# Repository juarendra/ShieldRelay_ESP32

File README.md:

# ShieldRelay_ESP32
Relay Shield for ESP32 , Nodemcu V2 Amica or Nodemcu V3 Lolin. In board there are 5 Relay and 3 type of Relay, first is 30A Relay Coil, second is 10 A Relay Coil and third is SSR 2A. And there are full extend header of Microcontroller. the power using Stepdown LM2596 with output 5V 3A and Input 5-30VDC. 

## Spesification ShieldRelay_ESP32
- Input Power 5-30VDC and stepdown to 5VDC
- PTC Fuse
- INPUT HEADER
- VCC HEADER
- VCC Selector 3v3 or 5V
- Supported ESP32 DEV KIT, NODEMCU V2 or V3
- Pin Header GPIO with Servo Formated
- 1 x 30A Relay Coil
- 2 x 10A Relay Couil
- 2 x 2A SSR

# Privew Hardware ShieldRelay_ESP32
<p align="center">

</p>

# Documentation 
- [Dimension](https://github.com/juarendra/ShieldRelay_ESP32/blob/main/HARDWARE/dimension_shield_esp32.pdf)
- [BOM](https://github.com/juarendra/ShieldRelay_ESP32/blob/main/DOC/BOM_shieldRelay.csv)

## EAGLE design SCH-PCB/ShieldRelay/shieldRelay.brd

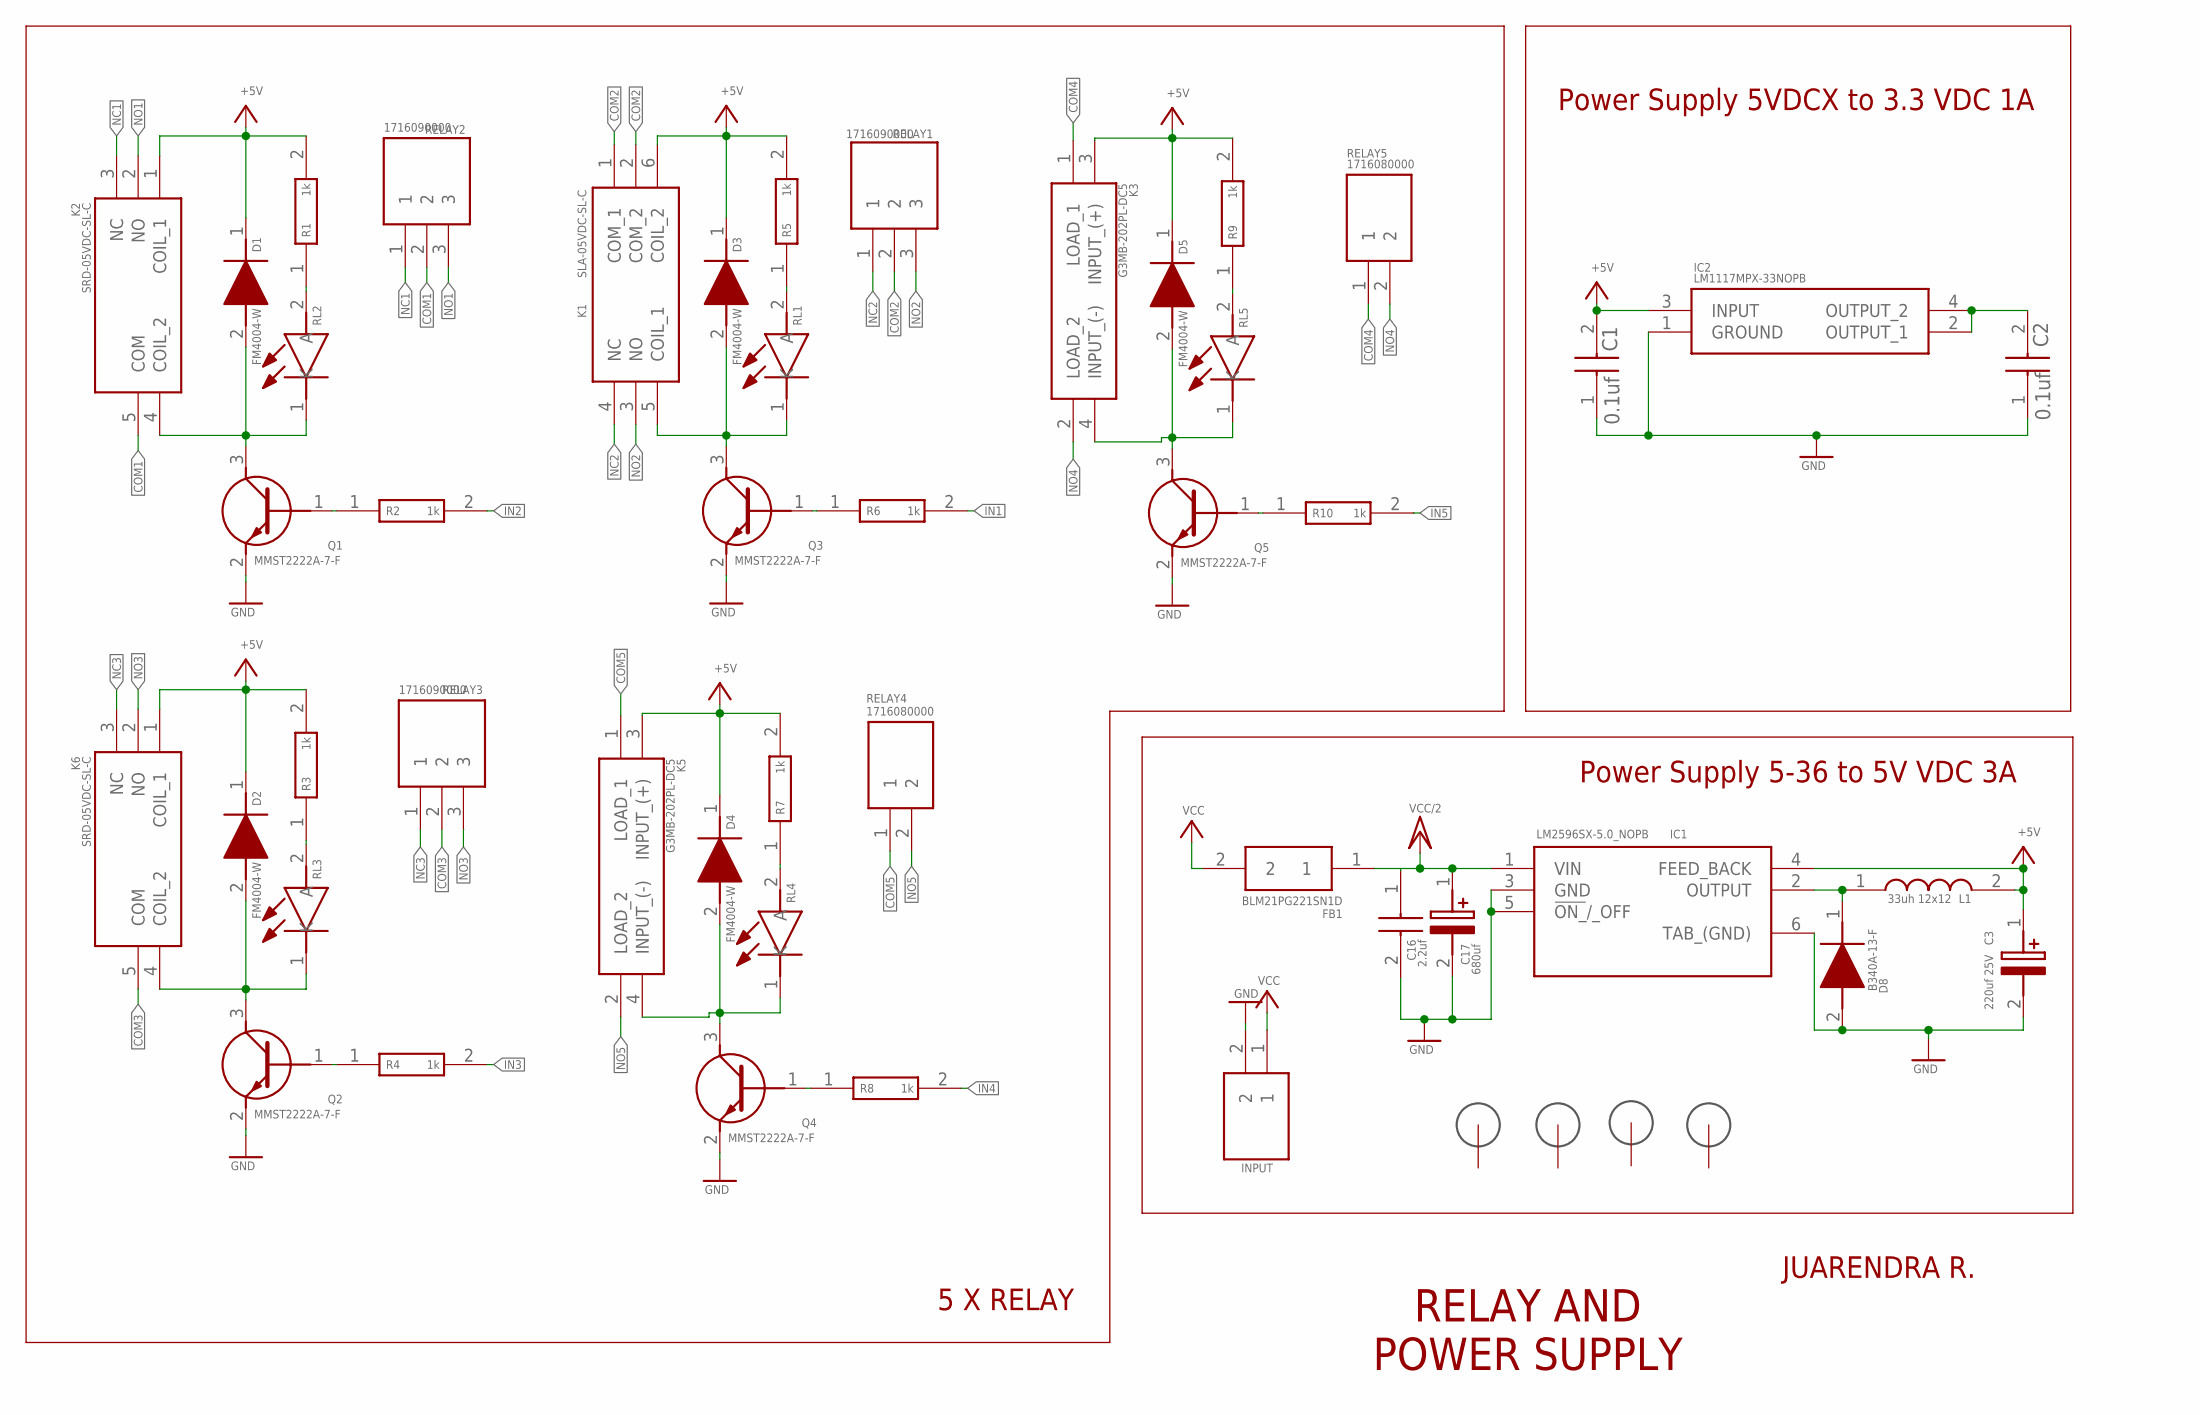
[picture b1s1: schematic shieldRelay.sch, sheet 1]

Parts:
C1, C2: 0.1uf; CAPC1608X95N
C3: 220uf 25V; CAPPRD350W60D850H1250
C16: 2.2uf; CAPC2012X140N
C17: 680uf; EEHZS1H221P
D1, D2, D3, D4, D5: FM4004-W; DIONM5025X231N
D8: B340A-13-F; DIOM5226X240N
FB1: BLM21PG221SN1D; BEADC2012X105N
H1, H2, H3, H4: 3MM_HOLE
IC1: LM2596SX-5.0_NOPB; KTT0005B
IC2: LM1117MPX-33NOPB; SOT230P700X180-4N
INPUT: 1759017; SHDRRA2W103P0X508_1X2_1016X120
K1: SLA-05VDC-SL-C; SLA05VDCSLC
K2, K6: SRD-05VDC-SL-C; SRD05VDCSLC
K3, K5: G3MB-202PL-DC5; G3MB202PLDC5
L1: 33uh 12x12; WE-PD_1260/1245/1280/121054
Q1, Q2, Q3, Q4, Q5: MMST2222A-7-F; SOT65P210X110-3N
R1, R2, R3, R4, R5, R6, R7, R8, R9, R10: 1k; ERA3AEB101V
RELAY1, RELAY2, RELAY3: 1716090000; SHDR3W95P0X508_1X3_1524X1000X1
RELAY4, RELAY5: 1716080000
RL1, RL2, RL3, RL4, RL5: 150080SS75000; LEDC2012X80N

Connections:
+5V: C1.2, C3.1 (+), D1.1 (K), D2.1 (K), D3.1 (K), D4.1 (K), D5.1 (K), IC1.4 (FEED_BACK), IC2.3 (INPUT), K1.6 (COIL_2), K2.1 (COIL_1), K3.3 (INPUT_(+)), K5.3 (INPUT_(+)), K6.1 (COIL_1), L1.2, R1.2, R3.2, R5.2, R7.2, R9.2; also elsewhere on the board
COM1: K2.5 (COM), RELAY2.2
COM2: K1.1 (COM_1), K1.2 (COM_2), RELAY1.2
COM3: K6.5 (COM), RELAY3.2
COM4: K3.1 (LOAD_1), RELAY5.1
COM5: K5.1 (LOAD_1), RELAY4.1
GND: C1.1, C2.1, C3.2 (-), C16.2, C17.2 (-), D8.2 (A), IC1.3 (GND), IC1.5 (!ON_!/_OFF), IC1.6 (TAB_(GND)), IC2.1 (GROUND), INPUT.2, Q1.2 (E), Q2.2 (E), Q3.2 (E), Q4.2 (E), Q5.2 (E); also elsewhere on the board
IN1: R6.2; also elsewhere on the board
IN2: R2.2; also elsewhere on the board
IN3: R4.2; also elsewhere on the board
IN4: R8.2; also elsewhere on the board
IN5: R10.2; also elsewhere on the board
unnamed: R3.1, RL3.2 (A)
unnamed: R1.1, RL2.2 (A)
unnamed: D1.2 (A), K2.4 (COIL_2), Q1.3 (C), RL2.1 (K)
unnamed: Q1.1 (B), R2.1
unnamed: D2.2 (A), K6.4 (COIL_2), Q2.3 (C), RL3.1 (K)
unnamed: Q2.1 (B), R4.1
unnamed: R5.1, RL1.2 (A)
unnamed: D3.2 (A), K1.5 (COIL_1), Q3.3 (C), RL1.1 (K)
unnamed: Q3.1 (B), R6.1
unnamed: R7.1, RL4.2 (A)
unnamed: D4.2 (A), K5.4 (INPUT_(-)), Q4.3 (C), RL4.1 (K)
unnamed: Q4.1 (B), R8.1
unnamed: R9.1, RL5.2 (A)
unnamed: D5.2 (A), K3.4 (INPUT_(-)), Q5.3 (C), RL5.1 (K)
unnamed: Q5.1 (B), R10.1
unnamed: D8.1 (K), IC1.2 (OUTPUT), L1.1
unnamed: C2.2, IC2.2 (OUTPUT_1), IC2.4 (OUTPUT_2)
NC1: K2.3 (NC), RELAY2.1
NC2: K1.4 (NC), RELAY1.1
NC3: K6.3 (NC), RELAY3.1
NO1: K2.2 (NO), RELAY2.3
NO2: K1.3 (NO), RELAY1.3
NO3: K6.2 (NO), RELAY3.3
NO4: K3.2 (LOAD_2), RELAY5.2
NO5: K5.2 (LOAD_2), RELAY4.2
VCC: FB1.2, INPUT.1
VCC/2: C16.1, C17.1 (+), FB1.1, IC1.1 (VIN); also elsewhere on the board

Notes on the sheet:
Power Supply 5-36 to 5V VDC 3A
5 X RELAY
Power Supply 5VDCX to 3.3 VDC 1A
RELAY AND POWER SUPPLY
JUARENDRA R.

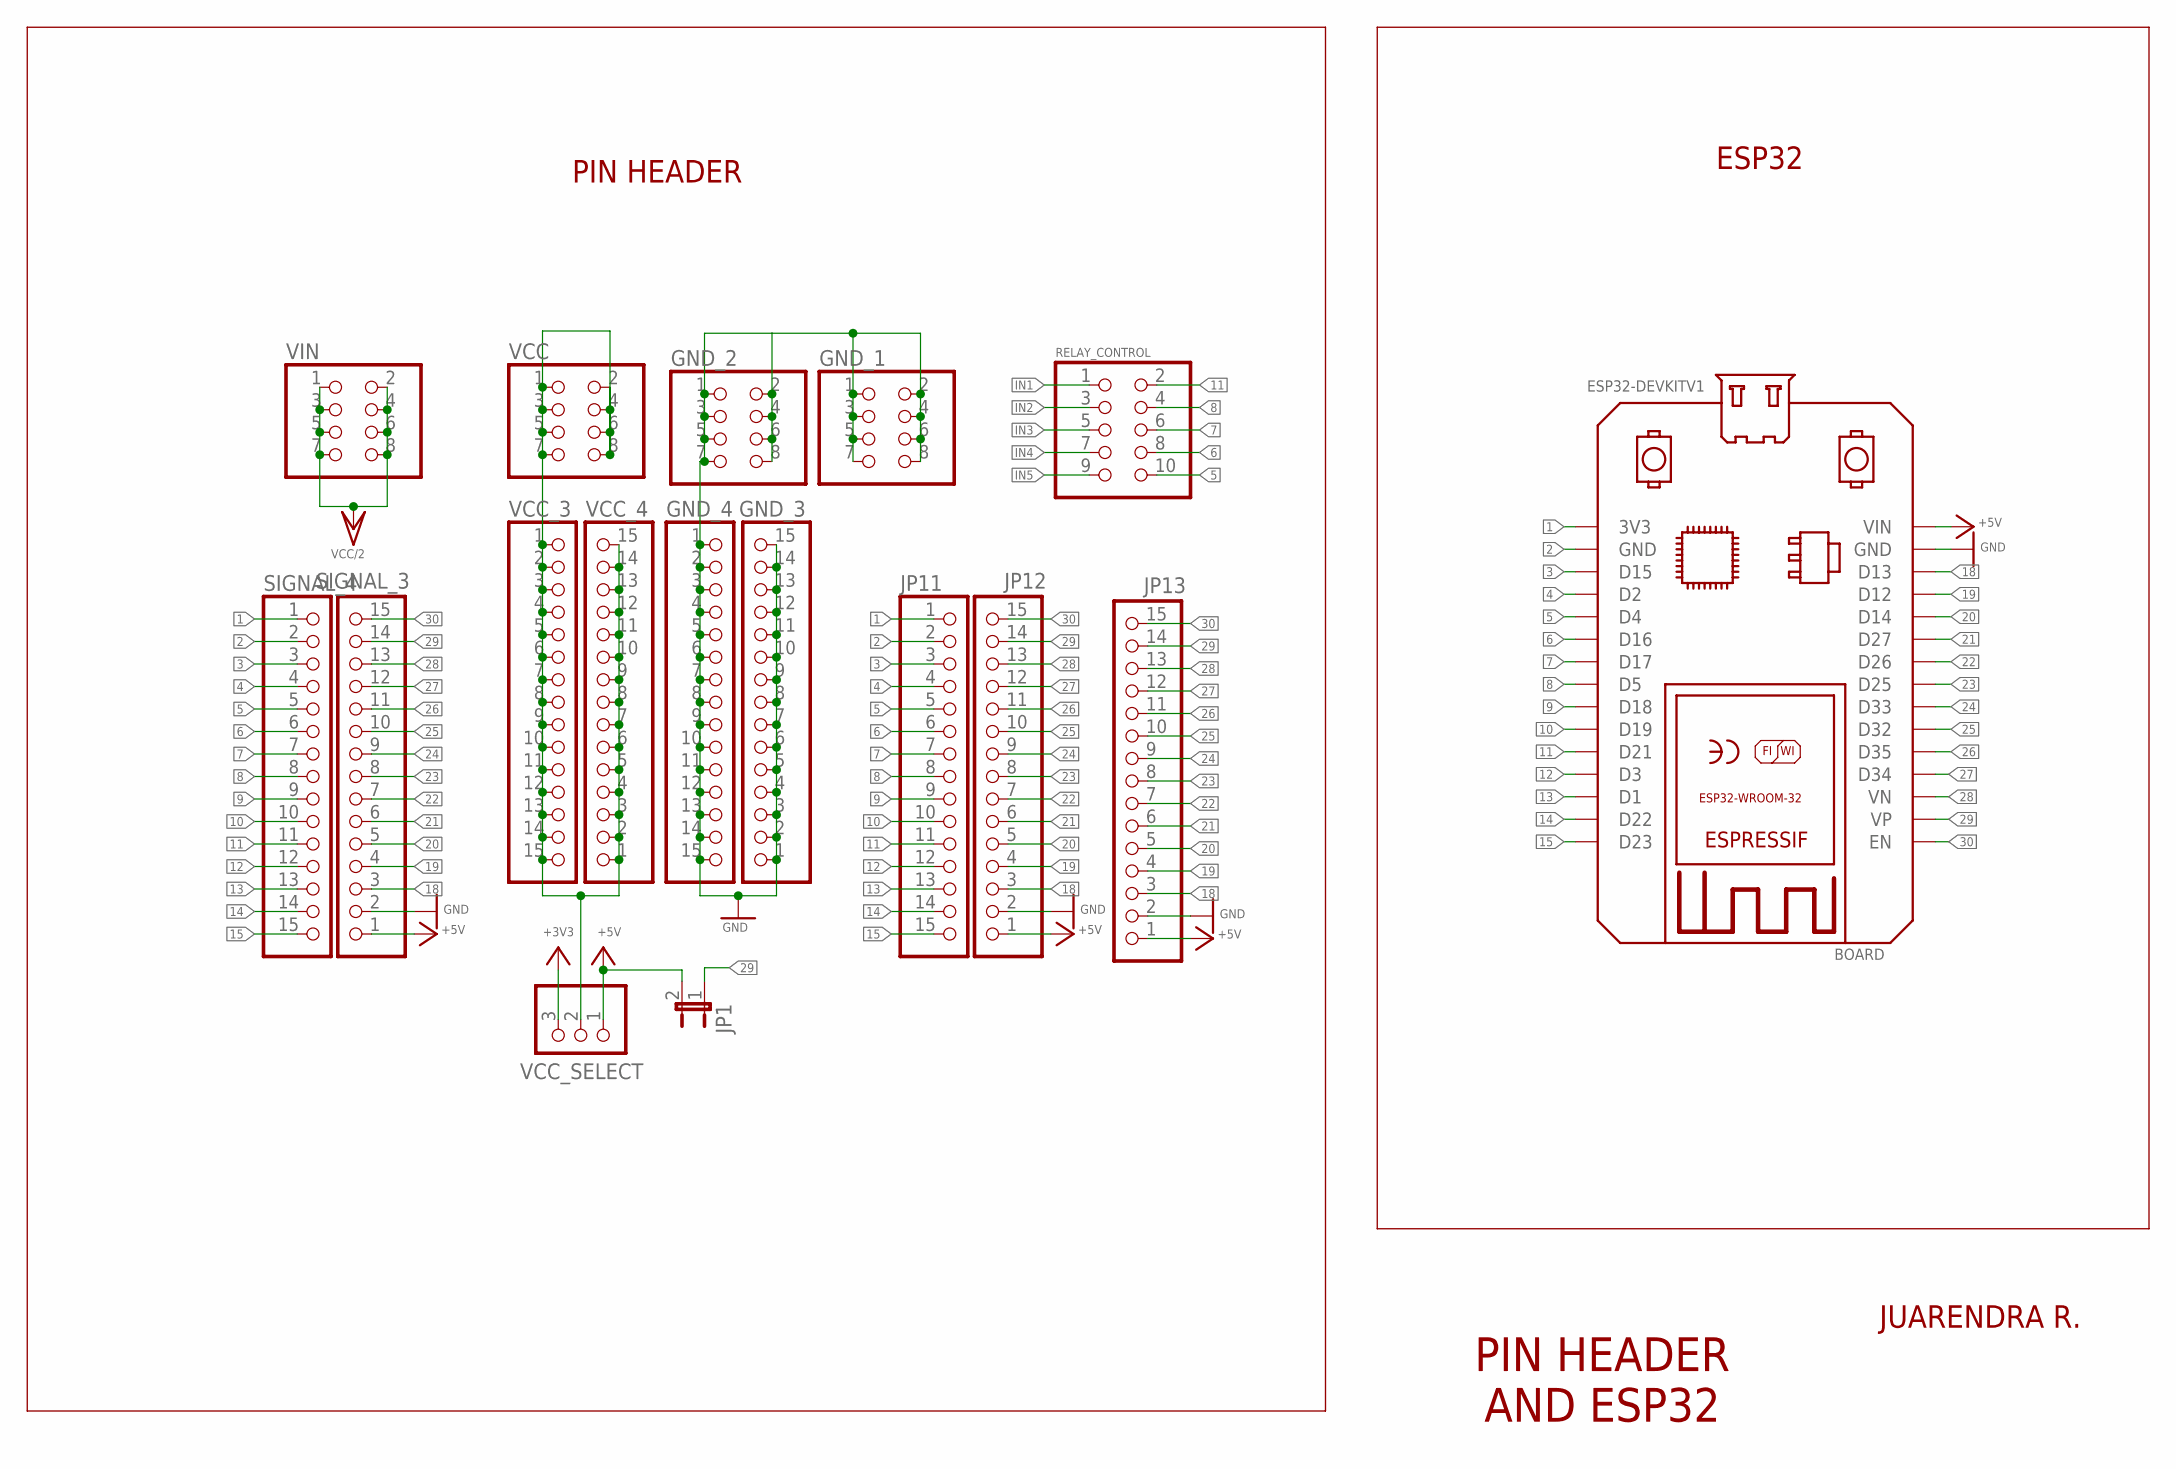
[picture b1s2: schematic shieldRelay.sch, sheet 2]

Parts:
BOARD: ESP32DEVKITV1; ESP32-DEVKITV1
GND_1, GND_2: PINHD-2X4; 2X04
GND_3, GND_4: PINHD-1X15; 1X15
JP1: JP1E; JP1
JP11, JP12, JP13: PINHD-1X15; 1X15
RELAY_CONTROL: PINHD-2X5; 2X05
SIGNAL_3, SIGNAL_4: PINHD-1X15; 1X15
VCC: PINHD-2X4; 2X04
VCC_3, VCC_4: PINHD-1X15; 1X15
VCC_SELECT: PINHD-1X3; 1X03
VIN: PINHD-2X4; 2X04

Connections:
1: BOARD.3V3, JP11.1, SIGNAL_4.1
2: BOARD.GND@1 (GND), JP11.2, SIGNAL_4.2
3: BOARD.D15, JP11.3, SIGNAL_4.3
4: BOARD.D2, JP11.4, SIGNAL_4.4
5: BOARD.D4, JP11.5, RELAY_CONTROL.10, SIGNAL_4.5
6: BOARD.D16, JP11.6, RELAY_CONTROL.8, SIGNAL_4.6
7: BOARD.D17, JP11.7, RELAY_CONTROL.6, SIGNAL_4.7
8: BOARD.D5, JP11.8, RELAY_CONTROL.4, SIGNAL_4.8
9: BOARD.D18, JP11.9, SIGNAL_4.9
10: BOARD.D19, JP11.10, SIGNAL_4.10
11: BOARD.D21, JP11.11, RELAY_CONTROL.2, SIGNAL_4.11
12: BOARD.D3, JP11.12, SIGNAL_4.12
13: BOARD.D1, JP11.13, SIGNAL_4.13
14: BOARD.D22, JP11.14, SIGNAL_4.14
15: BOARD.D23, JP11.15, SIGNAL_4.15
18: BOARD.D13, JP12.3, JP13.3, SIGNAL_3.3
19: BOARD.D12, JP12.4, JP13.4, SIGNAL_3.4
20: BOARD.D14, JP12.5, JP13.5, SIGNAL_3.5
21: BOARD.D27, JP12.6, JP13.6, SIGNAL_3.6
22: BOARD.D26, JP12.7, JP13.7, SIGNAL_3.7
23: BOARD.D25, JP12.8, JP13.8, SIGNAL_3.8
24: BOARD.D33, JP12.9, JP13.9, SIGNAL_3.9
25: BOARD.D32, JP12.10, JP13.10, SIGNAL_3.10
26: BOARD.D35, JP12.11, JP13.11, SIGNAL_3.11
27: BOARD.D34, JP12.12, JP13.12, SIGNAL_3.12
28: BOARD.VN, JP12.13, JP13.13, SIGNAL_3.13
29: BOARD.VP, JP1.1, JP12.14, JP13.14, SIGNAL_3.14
30: BOARD.EN, JP12.15, JP13.15, SIGNAL_3.15
+3V3: VCC_SELECT.3
+5V: BOARD.VIN, JP1.2, JP12.1, JP13.1, SIGNAL_3.1, VCC_SELECT.1; also elsewhere on the board
GND: BOARD.GND, GND_1.1, GND_1.2, GND_1.3, GND_1.4, GND_1.5, GND_1.6, GND_1.7, GND_1.8, GND_2.1, GND_2.2, GND_2.3, GND_2.4, GND_2.5, GND_2.6, GND_2.7, GND_2.8, GND_3.1, GND_3.2, GND_3.3, GND_3.4, GND_3.5, GND_3.6, GND_3.7, GND_3.8, GND_3.9, GND_3.10, GND_3.11, GND_3.12, GND_3.13, GND_3.14, GND_3.15, GND_4.1, GND_4.2, GND_4.3, GND_4.4, GND_4.5, GND_4.6, GND_4.7, GND_4.8, GND_4.9, GND_4.10, GND_4.11, GND_4.12, GND_4.13, GND_4.14, GND_4.15, JP12.2, JP13.2, SIGNAL_3.2; also elsewhere on the board
IN1: RELAY_CONTROL.1; also elsewhere on the board
IN2: RELAY_CONTROL.3; also elsewhere on the board
IN3: RELAY_CONTROL.5; also elsewhere on the board
IN4: RELAY_CONTROL.7; also elsewhere on the board
IN5: RELAY_CONTROL.9; also elsewhere on the board
unnamed: VCC.1, VCC.2, VCC.3, VCC.4, VCC.5, VCC.6, VCC.7, VCC.8, VCC_3.1, VCC_3.2, VCC_3.3, VCC_3.4, VCC_3.5, VCC_3.6, VCC_3.7, VCC_3.8, VCC_3.9, VCC_3.10, VCC_3.11, VCC_3.12, VCC_3.13, VCC_3.14, VCC_3.15, VCC_4.1, VCC_4.2, VCC_4.3, VCC_4.4, VCC_4.5, VCC_4.6, VCC_4.7, VCC_4.8, VCC_4.9, VCC_4.10, VCC_4.11, VCC_4.12, VCC_4.13, VCC_4.14, VCC_4.15, VCC_SELECT.2
VCC/2: VIN.1, VIN.2, VIN.3, VIN.4, VIN.5, VIN.6, VIN.7, VIN.8; also elsewhere on the board

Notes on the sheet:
PIN HEADER AND ESP32
JUARENDRA R.
PIN HEADER
ESP32

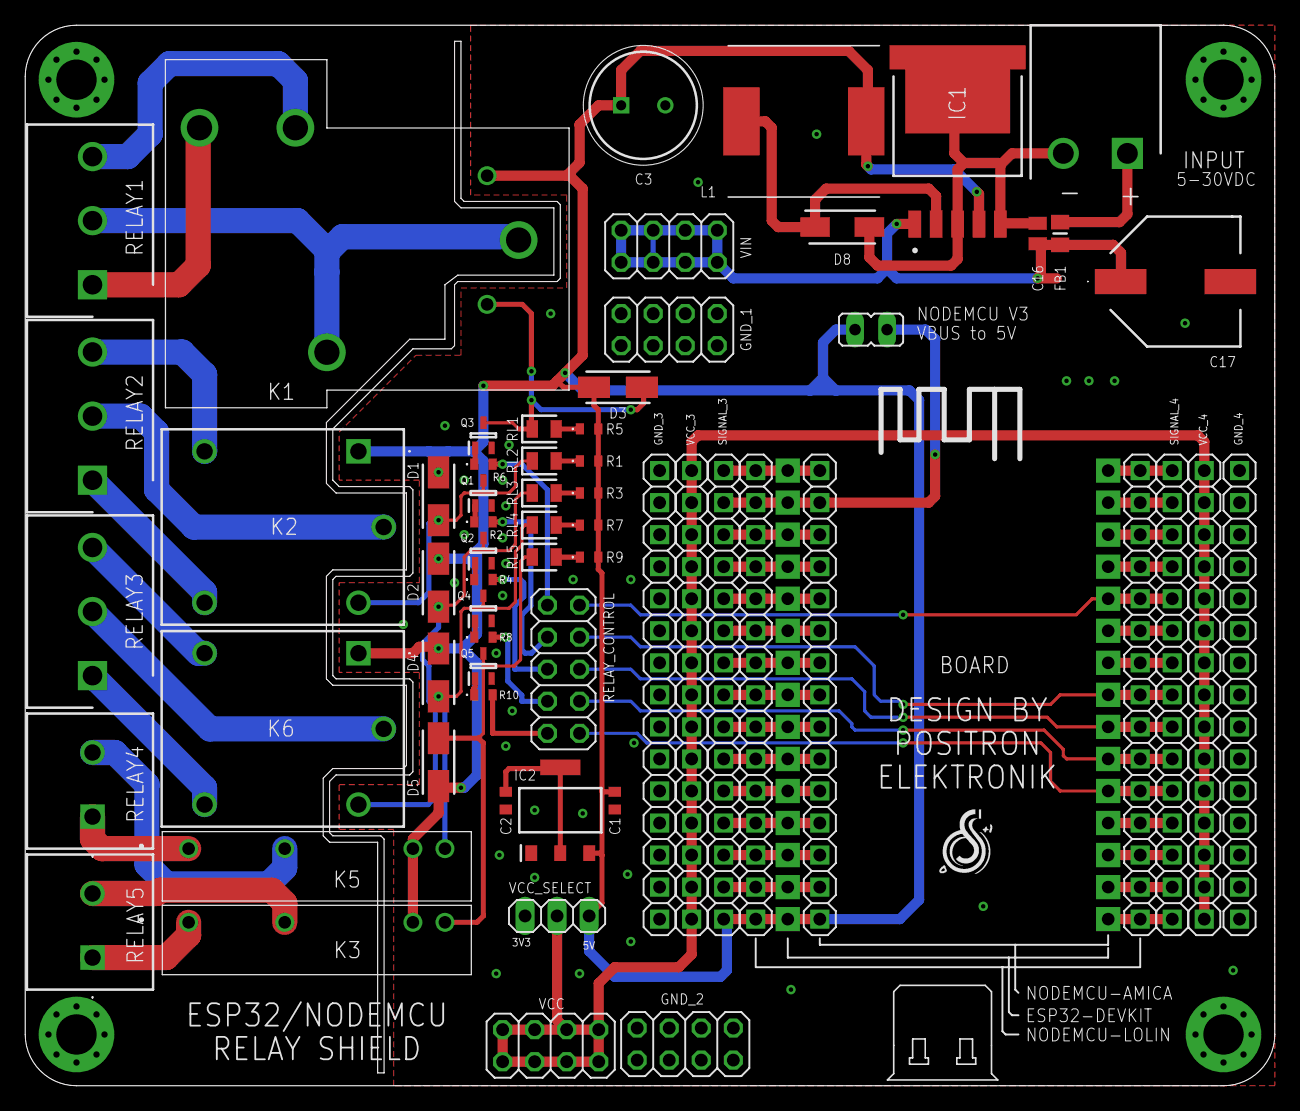
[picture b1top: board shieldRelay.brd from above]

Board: 2 copper layers, 99.1 x 84.1 mm, 67 parts (1 on the bottom side), 68 nets.

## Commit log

2024-05-20 FEAT: add first pcb
2024-05-22 FEAT: update library esp32 and remove nodemcu v2
2024-05-22 FEAT: Positioning component
2024-05-23 FEAT: update library pinhead
2024-05-23 FEAT: update library esp32-dev
2024-05-24 FEAT: update schematic
2024-05-24 FEAT: add 3v3 regulator
2024-05-24 FEAT: update board
2024-05-24 FEAT: update terminal block
2024-05-25 DOC: UPDATE SCHEMATIC, BOARD AND ADD PDF
2024-05-26 FEAT: add 3D model
2024-05-26 FEAT: add gerber file
2024-05-27 DOC: add documents hardware
2024-05-27 FEAT: Add plate
2024-05-27 DOC: add documents on README
2024-05-28 DOC: add BOM
2024-05-31 FEAT: add 5VDC to VBUS Jumper
2024-06-14 FIX: fix relay not connected to pin esp32
2024-06-15 DOC: update readme
2024-06-18 FIX: fix gnd pin on ic 1117 that no connected and placing name diode feedback relay
2024-07-19 FIX: fix reverse transistor relay
